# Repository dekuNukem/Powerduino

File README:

Powerduino - A fully programmable power strip with energy monitoring and wireless connectivity

A short introduction video: https://www.youtube.com/watch?v=ZPqnHy5OSVQ

Powerduino is a power strip that has been enhanced with a Teensy 3.1 microcontroller, RTC, current sensors, relays, WiFi module, external digital/analog IO pins, LCD, SD card, USB connector, and buttons. With an arsenal of new sensors and components, along with its open source design and Arduino compatible microcontroller, users are able to wirelessly control and monitor each socket over WiFi, observe real-time current, power and energy consumption of individual sockets, perform energy usage logging on SD card, and upload custom programs to the power strip through Arduino IDE to perform any action they want on each socket.

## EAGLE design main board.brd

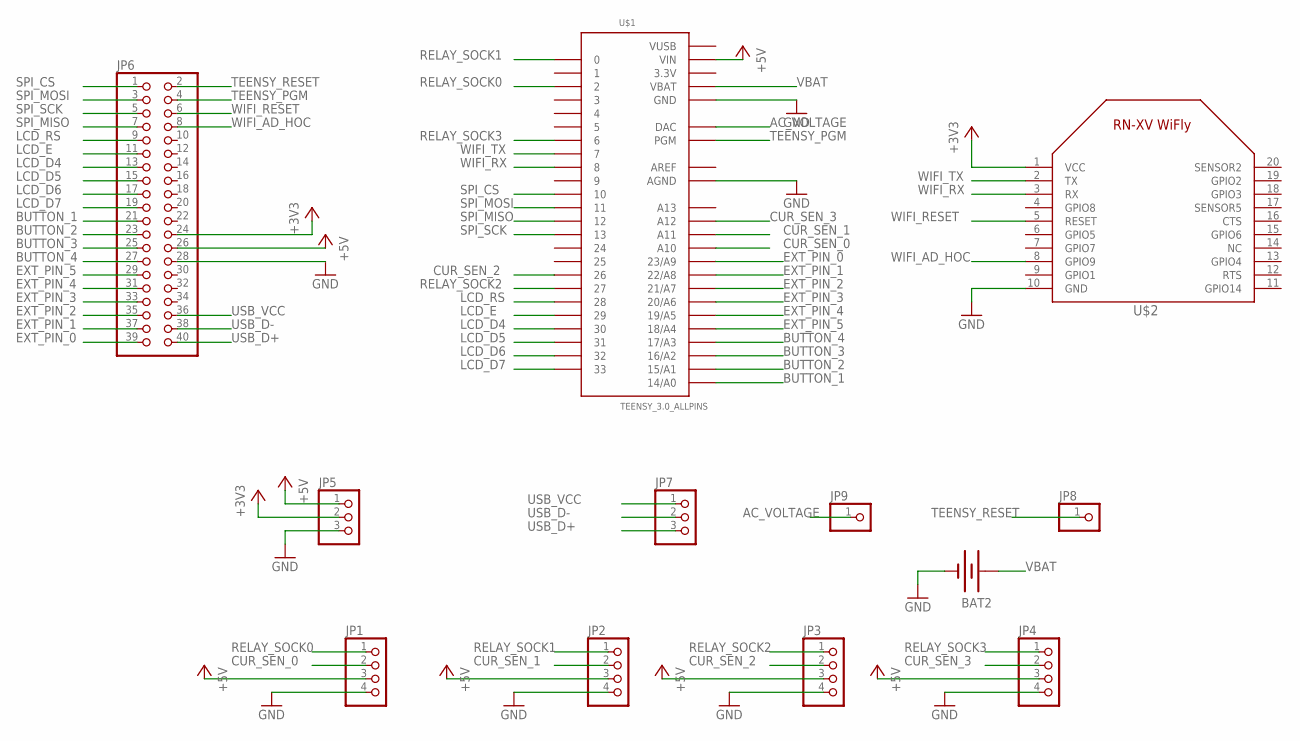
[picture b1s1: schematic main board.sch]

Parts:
BAT2: BATTERY20PTH; BATTCOM_20MM_PTH
JP1, JP2, JP3, JP4: PINHD-1X4/90; 1X04/90
JP5: PINHD-1X3/90; 1X03/90
JP6: PINHD-2X20; 2X20
JP7: PINHD-1X3; 1X03
JP8, JP9: PINHD-1X1; 1X01
U$1: TEENSY_3.0_ALLPINS
U$2: XBEEWIFLY; XBEE

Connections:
3.3V: U$1.3.3V, U$1.3.3V1 (3.3V), U$1.3.3V2 (3.3V)
+3V3: JP5.2, JP6.24, U$2.1 (VCC)
+5V: JP1.3, JP2.3, JP3.3, JP4.3, JP5.1, JP6.26, U$1.VIN
AC_VOLTAGE: JP9.1, U$1.RESET (DAC)
AREF: U$1.AREF
BUTTON_1: JP6.21, U$1.14/A0
BUTTON_2: JP6.23, U$1.15/A1
BUTTON_3: JP6.25, U$1.16/A2
BUTTON_4: JP6.27, U$1.17/A3
CUR_SEN_0: JP1.2, U$1.A10
CUR_SEN_1: JP2.2, U$1.A11
CUR_SEN_2: JP3.2, U$1.26
CUR_SEN_3: JP4.2, U$1.A12
EXT_PIN_0: JP6.39, U$1.23/A9
EXT_PIN_1: JP6.37, U$1.22/A8
EXT_PIN_2: JP6.35, U$1.21/A7
EXT_PIN_3: JP6.33, U$1.20/A6
EXT_PIN_4: JP6.31, U$1.19/A5
EXT_PIN_5: JP6.29, U$1.18/A4
GND: BAT2.2 (-), JP1.4, JP2.4, JP3.4, JP4.4, JP5.3, JP6.28, U$1.AGND, U$1.GND, U$1.GND1 (GND), U$1.GND2 (GND), U$2.10 (GND)
LCD_D4: JP6.13, U$1.30
LCD_D5: JP6.15, U$1.31
LCD_D6: JP6.17, U$1.32
LCD_D7: JP6.19, U$1.33
LCD_E: JP6.11, U$1.29
LCD_RS: JP6.9, U$1.28
RELAY_SOCK0: JP1.1, U$1.2
RELAY_SOCK1: JP2.1, U$1.0
RELAY_SOCK2: JP3.1, U$1.27
RELAY_SOCK3: JP4.1, U$1.6
SPI_CS: JP6.1, U$1.10
SPI_MISO: JP6.7, U$1.12
SPI_MOSI: JP6.3, U$1.11
SPI_SCK: JP6.5, U$1.13
TEENSY_PGM: JP6.4, U$1.PGM
TEENSY_RESET: JP6.2, JP8.1
USB_D+: JP6.40, JP7.3
USB_D-: JP6.38, JP7.2
USB_VCC: JP6.36, JP7.1
VBAT: BAT2.1 (+), U$1.VBAT
VUSB: U$1.VUSB
WIFI_AD_HOC: JP6.8, U$2.8 (GPIO9)
WIFI_RESET: JP6.6, U$2.5 (RESET)
WIFI_RX: U$1.8, U$2.3 (RX)
WIFI_TX: U$1.7, U$2.2 (TX)

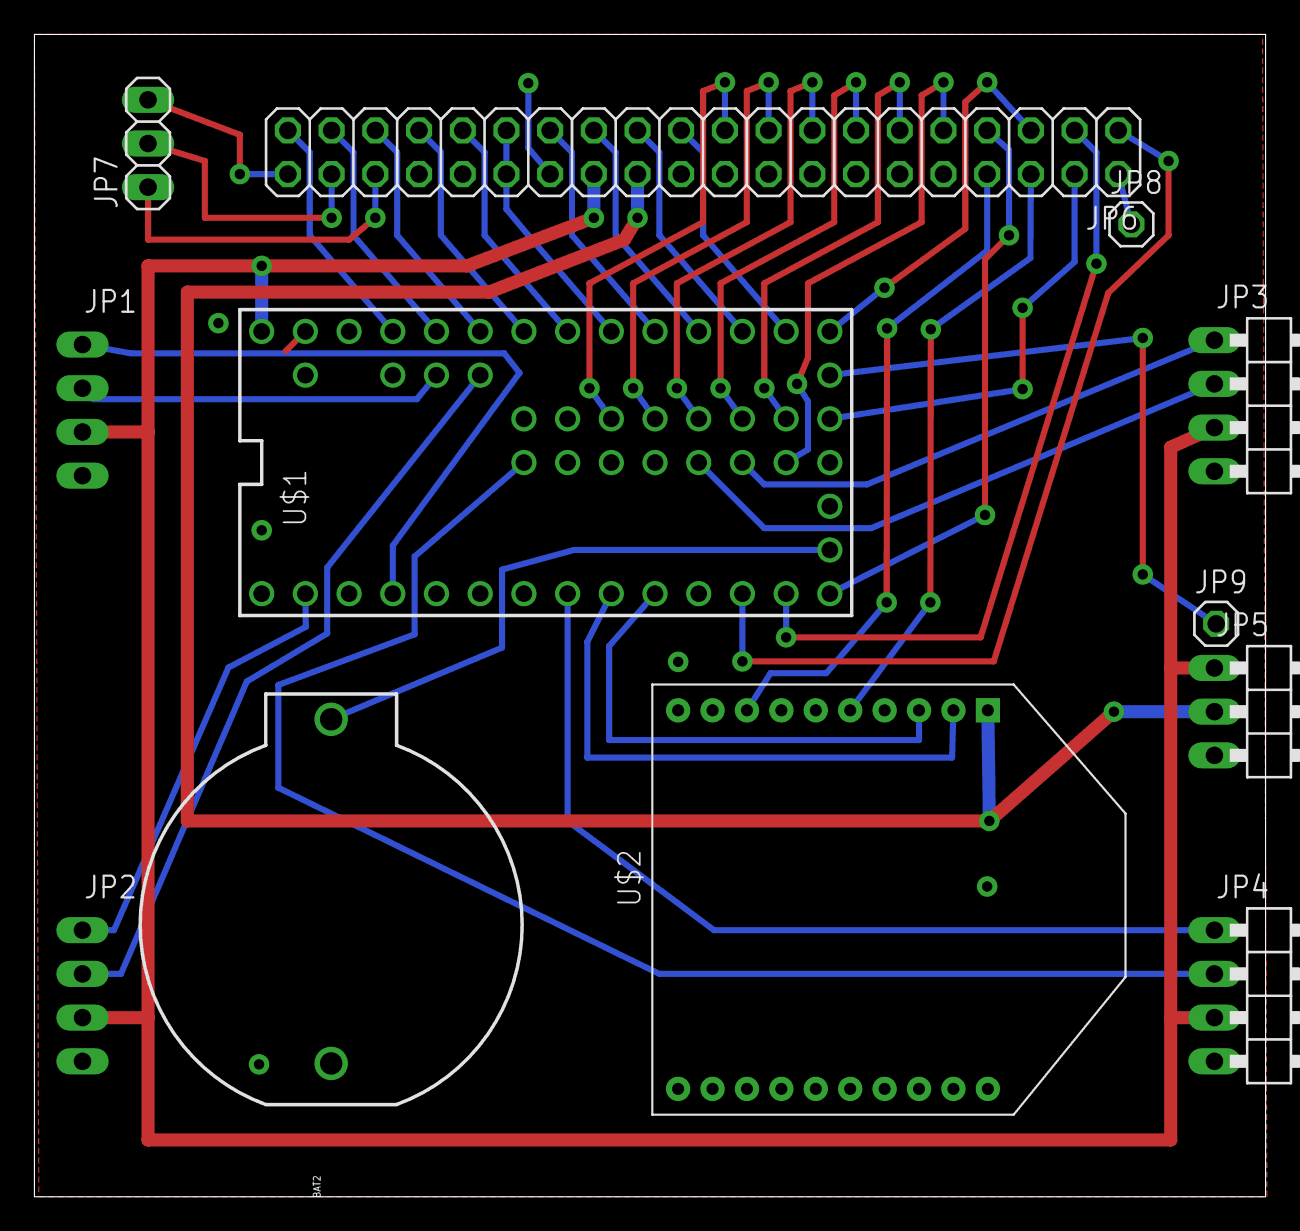
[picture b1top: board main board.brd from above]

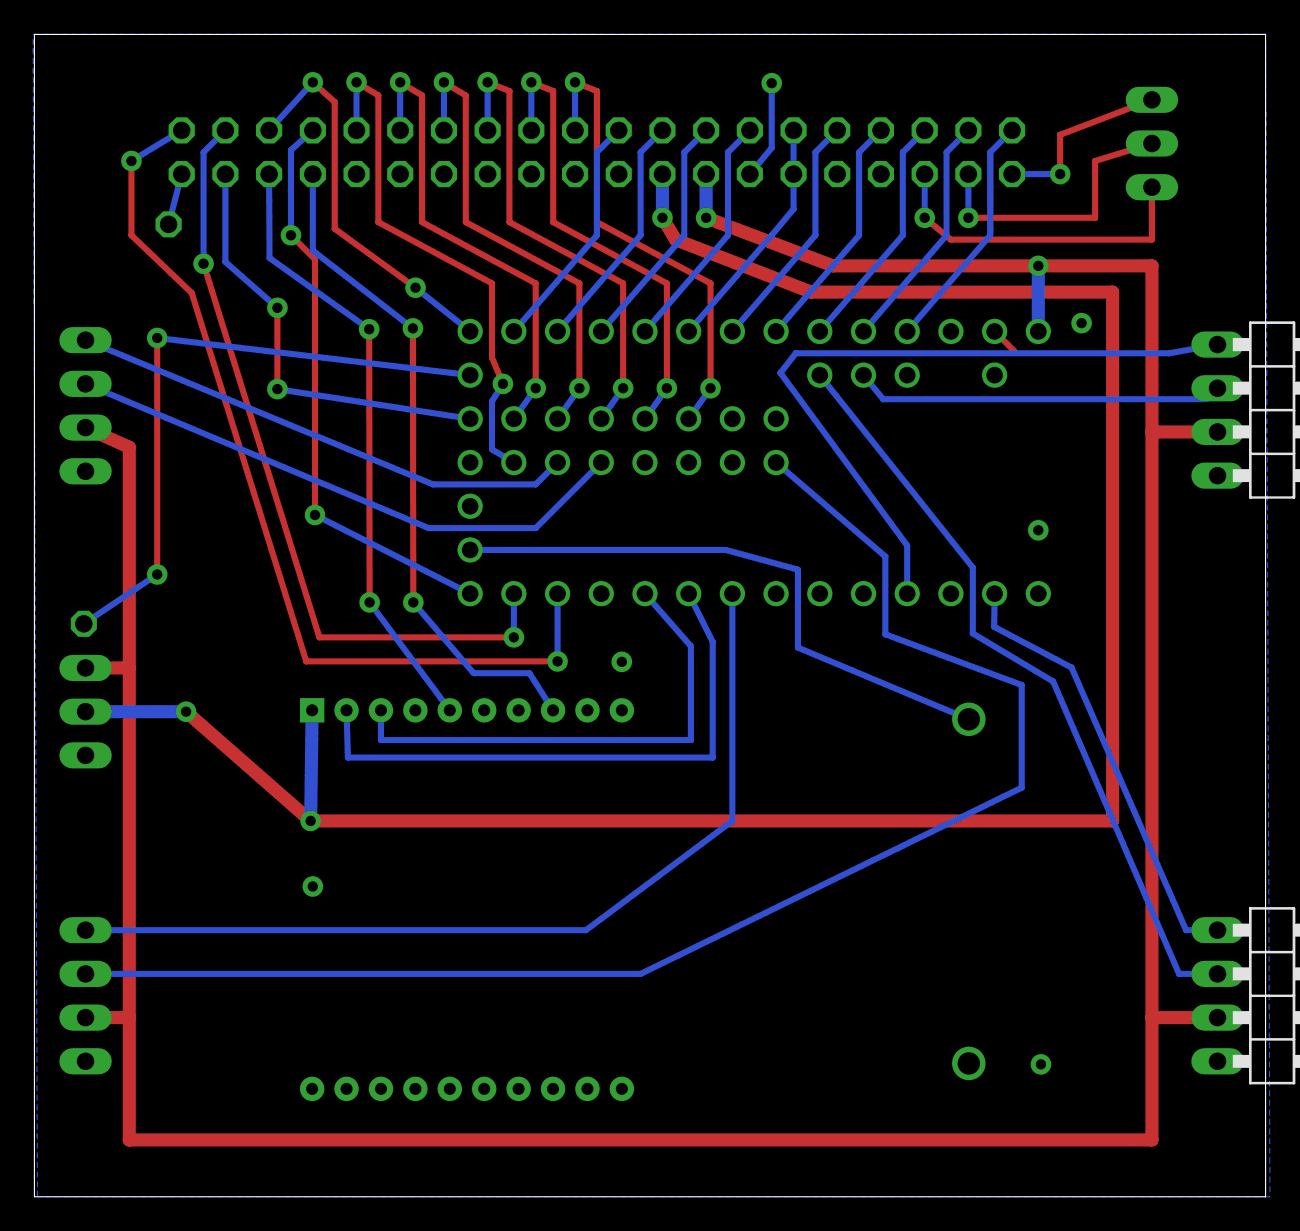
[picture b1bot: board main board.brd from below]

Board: 2 copper layers, 71.6 x 67.6 mm, 12 parts (2 on the bottom side), 43 nets.

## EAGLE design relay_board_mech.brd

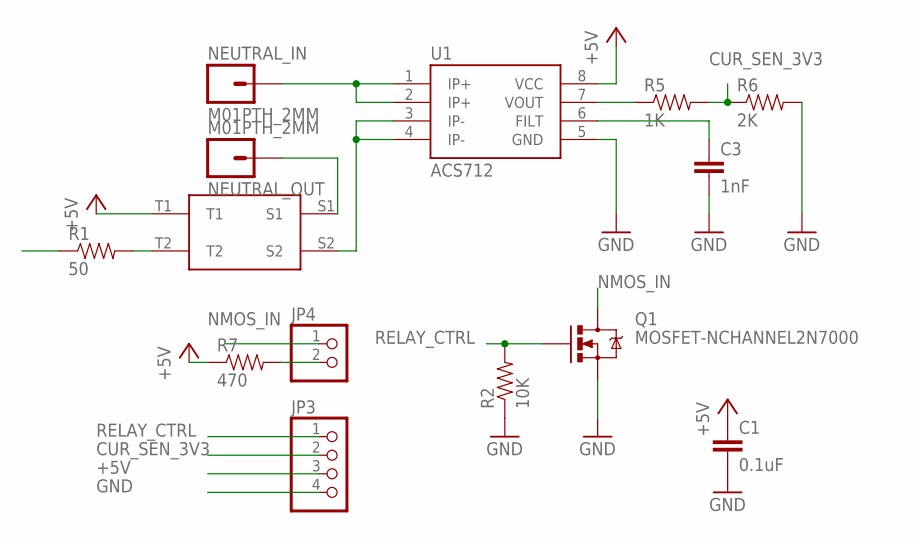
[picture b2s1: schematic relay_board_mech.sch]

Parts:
C1: 0.1uF; CAP-PTH-SMALLEZ
C3: 1nF; CAP-PTH-SMALLEZ
JP3: PINHD-1X4; 1X04
JP4: PINHD-1X2; 1X02
NEUTRAL_IN: M01PTH_2MM; 1X01_2MM
NEUTRAL_OUT: M01PTH_2MM; 1X01_2MM
Q1: MOSFET-NCHANNEL2N7000; TO-92
R1: 50; AXIAL-0.1
R2: 10K; AXIAL-0.1
R5: 1K; AXIAL-0.1
R6: 2K; AXIAL-0.1
R7: 470; AXIAL-0.1
U1: ACS712; SO08
U$1: T77S1D10-05

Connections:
+5V: C1.1, JP3.3, R7.P$1 (1), U1.8 (VCC), U$1.T1
CUR_SEN_3V3: JP3.2, R5.P$2 (2), R6.P$1 (1)
CUR_SEN_5V: R5.P$1 (1), U1.7 (VOUT)
GND: C1.2, C3.2, JP3.4, Q1.1 (S), R2.P$1 (1), R6.P$2 (2), U1.5 (GND)
unnamed: NEUTRAL_OUT.1, U$1.S1
unnamed: R1.P$2 (2), U$1.T2
unnamed: C3.1, U1.6 (FILT)
unnamed: NEUTRAL_IN.1, U1.1 (IP+), U1.2 (IP+)
unnamed: JP4.2, R7.P$2 (2)
unnamed: U1.3 (IP-), U1.4 (IP-), U$1.S2
NMOS_IN: JP4.1, Q1.3 (D), R1.P$1 (1)
RELAY_CTRL: JP3.1, Q1.2 (G), R2.P$2 (2)

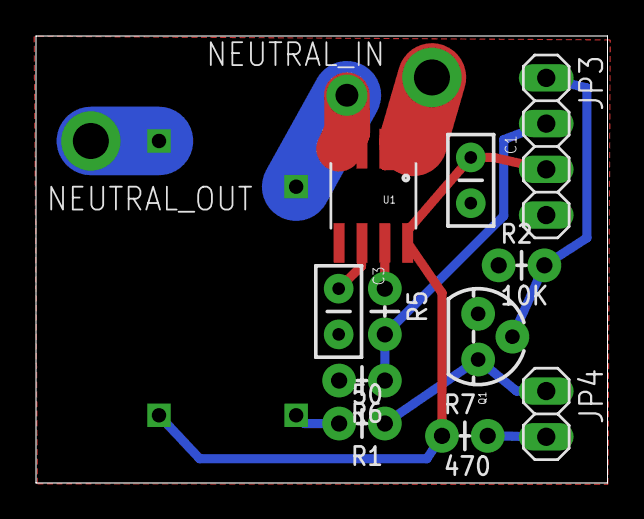
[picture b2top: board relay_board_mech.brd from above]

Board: 2 copper layers, 31.8 x 24.8 mm, 14 parts (0 on the bottom side), 12 nets.

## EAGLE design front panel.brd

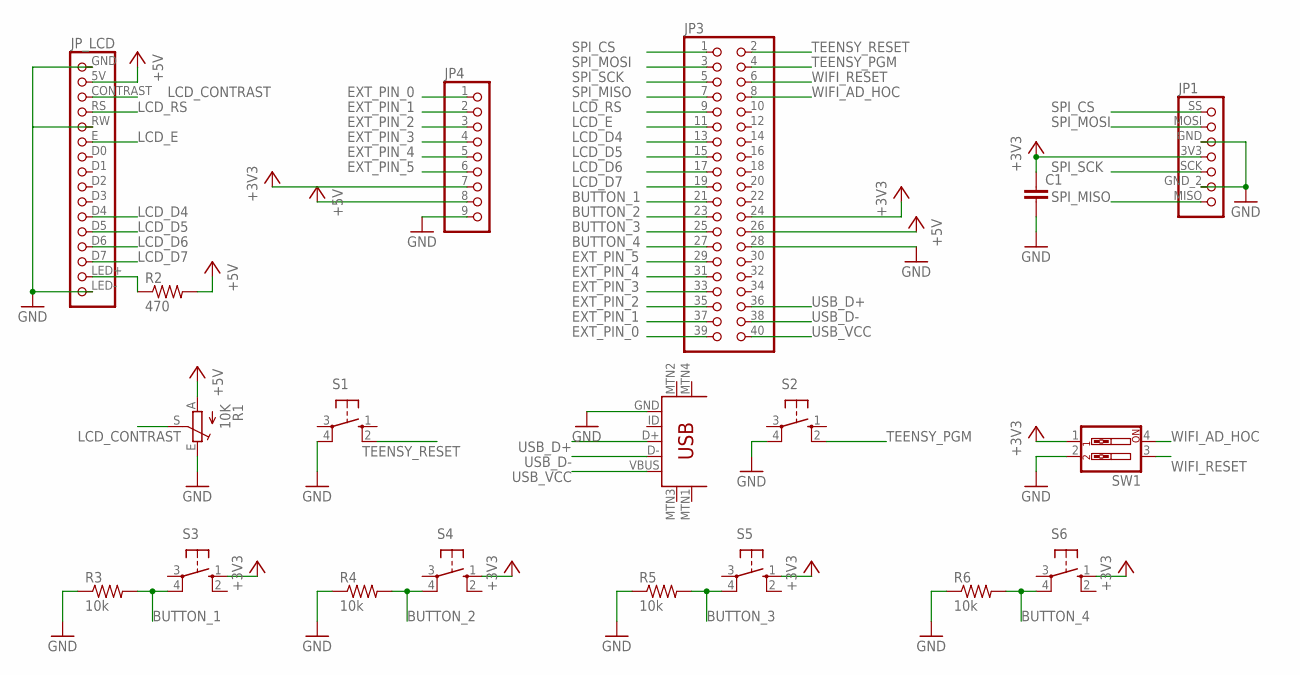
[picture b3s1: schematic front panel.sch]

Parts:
C1: 0.1UF-50V-20%(PTH)KIT-EZ; CAP-PTH-SMALL-KIT
JP1: PINHD-1X7; 1X07
JP3: PINHD-2X20; 2X20
JP4: PINHD-1X9; 1X09
JP_LCD: PINHD-1X16; 1X16
R1: 10K; CA6V
R2: 470; 0207/10
R3, R4, R5, R6: 10k; 0207/10
S1, S2, S3, S4, S5, S6: 10-XX; B3F-10XX
SW1: SW_DIP-2; EDG-02
U$1: USB-MINIB-5PIN; USB-MINIB

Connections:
+3V3: C1.1, JP1.3V3 (4), JP3.24, JP4.7, S3.1 (S), S4.1 (S), S5.1 (S), S6.1 (S), SW1.1
+5V: JP3.26, JP4.8, JP_LCD.5V, R1.A, R2.2
BUTTON_1: JP3.21, R3.2, S3.4 (P1)
BUTTON_2: JP3.23, R4.2, S4.4 (P1)
BUTTON_3: JP3.25, R5.2, S5.4 (P1)
BUTTON_4: JP3.27, R6.2, S6.4 (P1)
EXT_PIN_0: JP3.39, JP4.1
EXT_PIN_1: JP3.37, JP4.2
EXT_PIN_2: JP3.35, JP4.3
EXT_PIN_3: JP3.33, JP4.4
EXT_PIN_4: JP3.31, JP4.5
EXT_PIN_5: JP3.29, JP4.6
GND: C1.2, JP1.GND (3), JP1.GND_2 (6), JP3.28, JP4.9, JP_LCD.GND, JP_LCD.LED-, JP_LCD.RW, R1.E, R3.1, R4.1, R5.1, R6.1, S1.4 (P1), S2.4 (P1), SW1.2, U$1.GND
LCD_CONTRAST: JP_LCD.CONTRAST, R1.S
LCD_D4: JP3.13, JP_LCD.D4
LCD_D5: JP3.15, JP_LCD.D5
LCD_D6: JP3.17, JP_LCD.D6
LCD_D7: JP3.19, JP_LCD.D7
LCD_E: JP3.11, JP_LCD.E
LCD_RS: JP3.9, JP_LCD.RS
unnamed: JP_LCD.LED+, R2.1
SPI_CS: JP1.SS (1), JP3.1
SPI_MISO: JP1.MISO (7), JP3.7
SPI_MOSI: JP1.MOSI (2), JP3.3
SPI_SCK: JP1.SCK (5), JP3.5
TEENSY_PGM: JP3.4, S2.2 (S1)
TEENSY_RESET: JP3.2, S1.2 (S1)
USB_D+: JP3.36, U$1.D+
USB_D-: JP3.38, U$1.D-
USB_VCC: JP3.40, U$1.VBUS
WIFI_AD_HOC: JP3.8, SW1.4
WIFI_RESET: JP3.6, SW1.3

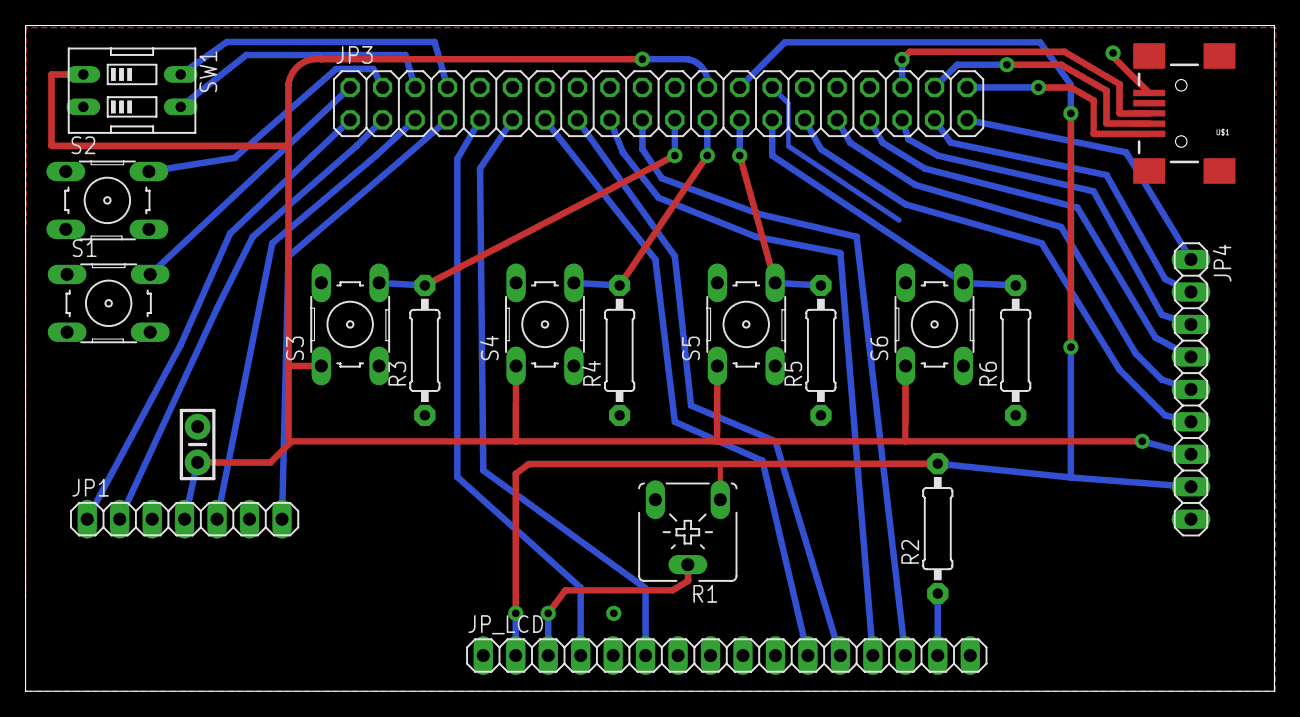
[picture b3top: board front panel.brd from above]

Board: 2 copper layers, 97.7 x 52.1 mm, 19 parts (0 on the bottom side), 32 nets.

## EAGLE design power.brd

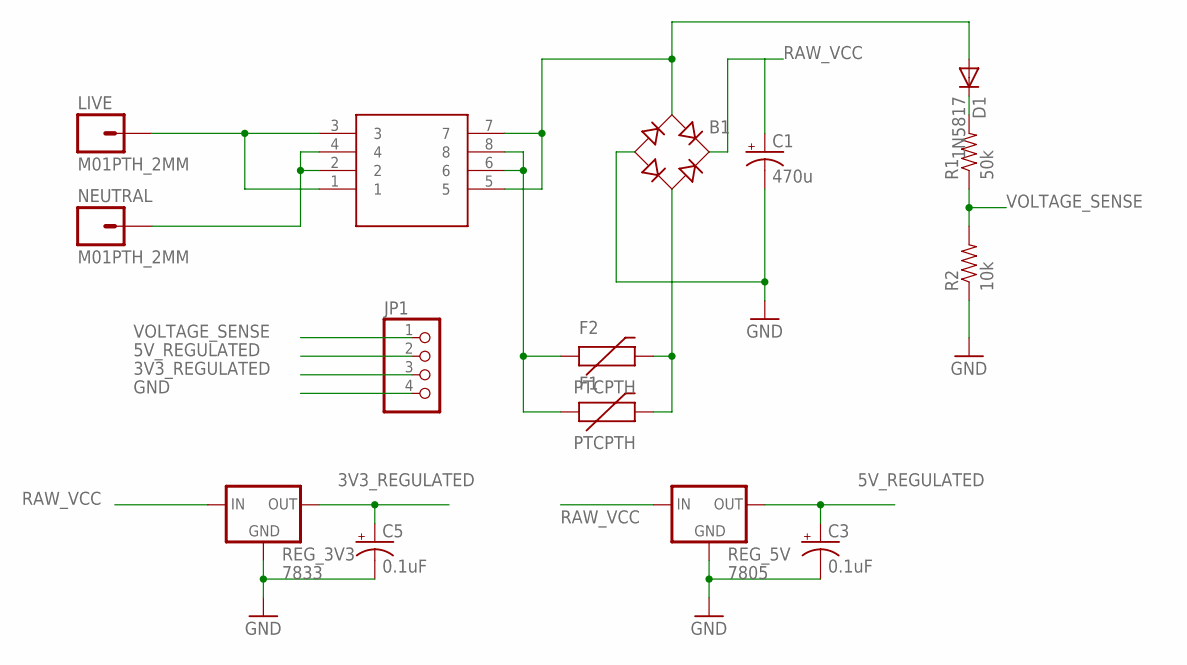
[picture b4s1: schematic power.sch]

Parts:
B1: RB1A
C1: 470u; E3,5-8
C3, C5: 0.1uF; CPOL-RADIAL-10UF-25V
D1: 1N5817; DO34-7
F1, F2: PTCPTH; PTC
JP1: PINHD-1X4; 1X04
LIVE: M01PTH_2MM; 1X01_2MM
NEUTRAL: M01PTH_2MM; 1X01_2MM
R1: 50k; AXIAL-0.3EZ
R2: 10k; AXIAL-0.3EZ
REG_3V3: 7833; TO220-IGO
REG_5V: 7805; TO220-IGO
U$1: FP16-150; FLATPACKXFORMER

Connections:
3V3_REGULATED: C5.1 (+), JP1.3, REG_3V3.OUT
5V_REGULATED: C3.1 (+), JP1.2, REG_5V.OUT
GND: B1.-, C1.-, C3.2 (-), C5.2 (-), JP1.4, R2.P$1 (1), REG_3V3.GND, REG_5V.GND
unnamed: F1.P$1 (1), F2.P$1 (1), U$1.6, U$1.8
unnamed: B1.AC2, F1.P$2 (2), F2.P$2 (2)
unnamed: LIVE.1, U$1.1, U$1.3
unnamed: D1.C, R1.P$2 (2)
unnamed: B1.AC1, D1.A, U$1.5, U$1.7
NEUTRAL_IN: NEUTRAL.1, U$1.2, U$1.4
RAW_VCC: B1.+, C1.+, REG_3V3.IN, REG_5V.IN
VOLTAGE_SENSE: JP1.1, R1.P$1 (1), R2.P$2 (2)

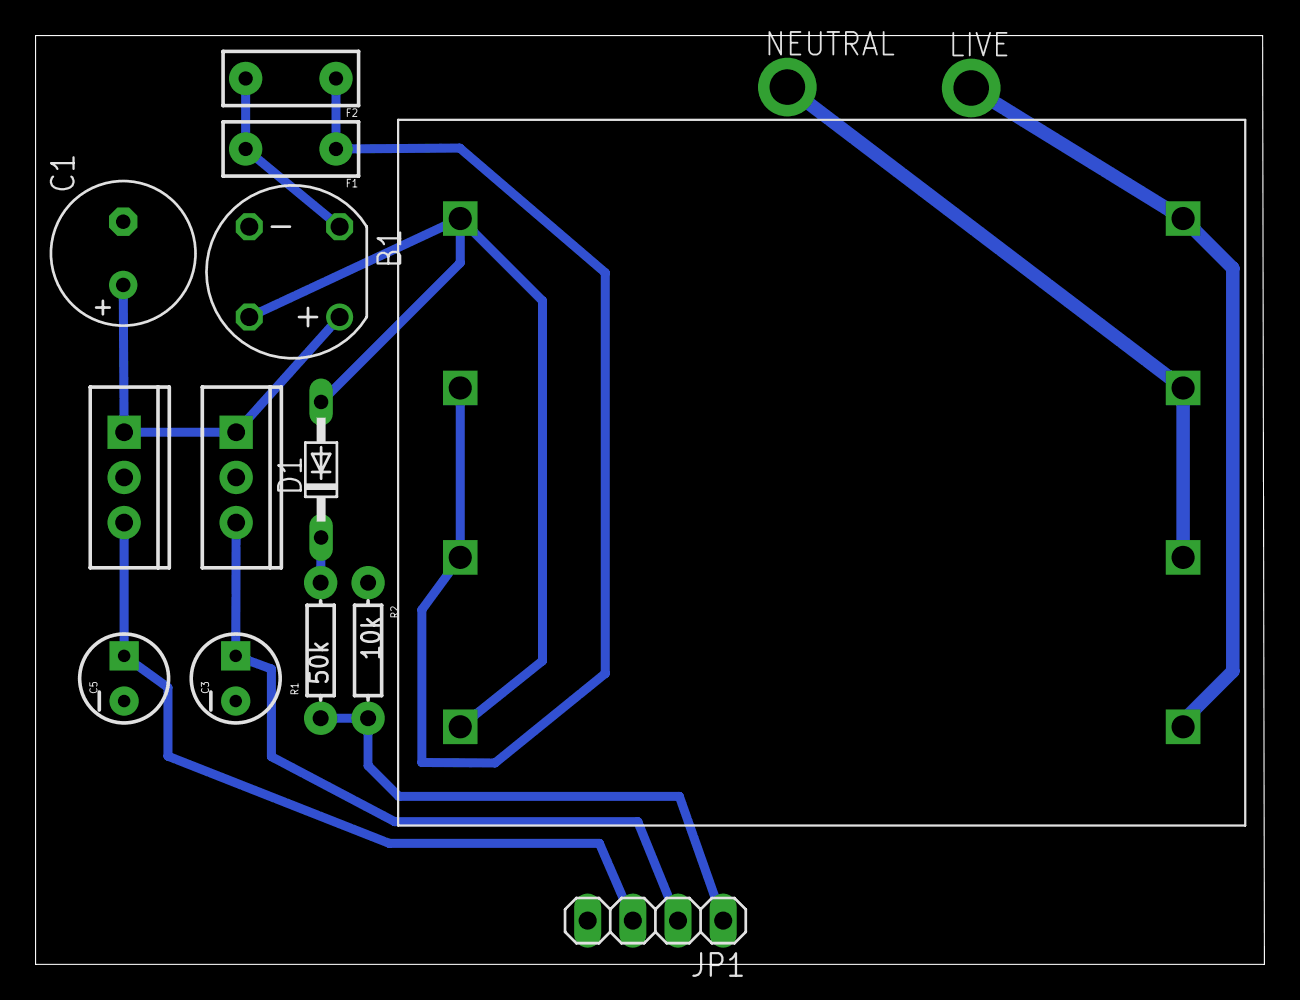
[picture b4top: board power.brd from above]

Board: 2 copper layers, 69.1 x 52.2 mm, 15 parts (0 on the bottom side), 11 nets.

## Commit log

2014-05-02 removed a executable
2014-05-02 license
2014-05-10 Update powerduino_uc.cpp
    Is better to use memset instead a loop!

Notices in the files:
parts and their libraries:
SparkFun-Capacitors: Licensing: Creative Commons ShareAlike 4.0 International - https://creativecommons.org/licenses/by-sa/4.0
